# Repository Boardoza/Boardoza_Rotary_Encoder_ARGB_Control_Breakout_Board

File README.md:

# Boardoza Rotary Encoder EC1101S Breakout Board

The **Boardoza Rotary Encoder EC1101S Breakout Board** is a multifunctional input and visual feedback solution that combines a **mechanical rotary encoder with an integrated push button** and **addressable RGB LEDs (ARGB)** on a single compact PCB. This board converts rotational motion into digital signals while simultaneously enabling dynamic visual effects through programmable LEDs.

By integrating **14 cascaded ARGB LEDs** directly around the encoder, the board allows users to visually represent rotation, direction, speed, or system states. Each encoder movement can be interpreted by a microcontroller (such as Arduino, ESP32, or similar platforms) to control LED color, brightness, and animation patterns, making it ideal for interactive interfaces, control panels, and creative electronics projects.

## [Click here to purchase!](https://www.ozdisan.com/ureticiler/boardoza)

| Front Side | Back Side |
|:---:|:---:|
|  |  |

---

## Key Features

- **Rotary Encoder with Push Button:** Mechanical rotary encoder with integrated momentary push button for menu navigation and user input.
- **Integrated Addressable RGB LEDs:** Features 14 cascaded ARGB LEDs for dynamic visual feedback and animation effects.
- **Quadrature Output Signals:** Provides A and B channel outputs for accurate direction and rotation detection.
- **Visual Motion Representation:** Encoder rotation can be visually expressed through programmable LED color, pattern, and brightness changes.
- **Wide Logic Compatibility:** Fully compatible with both 3.3 V and 5 V microcontroller systems.
- **Expandable LED Chain:** ARGB data and clock input/output pins allow cascading with additional LED boards.
- **20 Pulses per Revolution:** Provides 20 pulses per 360° rotation (per phase) for precise rotational detection.

---

## Technical Specifications  

**Model:** Rotary Encoder EC1101S  
**Manufacturer:** Boardoza  
**Encoder Type:** Mechanical rotary encoder with push button  
**LED Type:** Addressable RGB (ARGB)  
**Number of LEDs:** 14  
**LED Interface:** Serial Data (DIN/DOUT), Clock (CIN/COUT)  
**Signal Outputs:** Encoder A, Encoder B, Push Button (SW)  
**Input Voltage:** 3.3 V / 5 V  
**Logic Level:** 3.3 V / 5 V compatible  
**Operating Temperature:** -40 °C to +85 °C  
**Board Dimensions:** 40 mm × 40 mm  

---

## Board Pinout

### **( J1 ) Main Connector**

| Pin Number | Pin Name | Description |
|:---:|:---:|---|
| 1 | VCC (3V3–5V) | Power supply input |
| 2 | SW | Encoder push button output (Active Low) |
| 3 | DOUT | ARGB serial data output |
| 4 | COUT | ARGB clock output |
| 5 | CIN | ARGB clock input |
| 6 | DIN | ARGB serial data input |
| 7 | Terminal_B | Encoder B channel output |
| 8 | Terminal_A | Encoder A channel output |
| 9 | GND | Ground |

---

## Board Dimensions

---

## Step Files

[Boardoza ROTARY ENCODER.step](./assets/B-ROTARY%20ENCODER_EC1101S%20Step.step)

---

## Datasheet

- [PLCC IC + RGB LEDs Datasheet.pdf](./assets/PLCC%20IC+RGB%20LEDs%20Datasheet.pdf)  
- [ROTARY ENCODER EC1101S Breakout Datasheet.pdf](./assets/B-ROTARY%20ENCODER_EC1101S%20Datasheet.pdf)

---

## Version History

- **V1.0.0** – Initial Release

---

## Support

- For questions or technical support, please contact **support@boardoza.com**

---

## **License**

This repository contains both hardware and software components:

### **Hardware Design**

[![CC BY-SA 4.0][cc-by-sa-shield]][cc-by-sa]

All hardware design files are licensed under [Creative Commons Attribution-ShareAlike 4.0 International License][cc-by-sa].

[cc-by-sa]: http://creativecommons.org/licenses/by-sa/4.0/
[cc-by-sa-shield]: https://img.shields.io/badge/License-CC%20BY--SA%204.0-lightgrey.svg

### **Software/Firmware**

[![BSD-3-Clause][bsd-shield]][bsd]

All software and firmware are licensed under [BSD 3-Clause License][bsd].

[bsd]: https://opensource.org/licenses/BSD-3-Clause
[bsd-shield]: https://img.shields.io/badge/License-BSD%203--Clause-blue.svg

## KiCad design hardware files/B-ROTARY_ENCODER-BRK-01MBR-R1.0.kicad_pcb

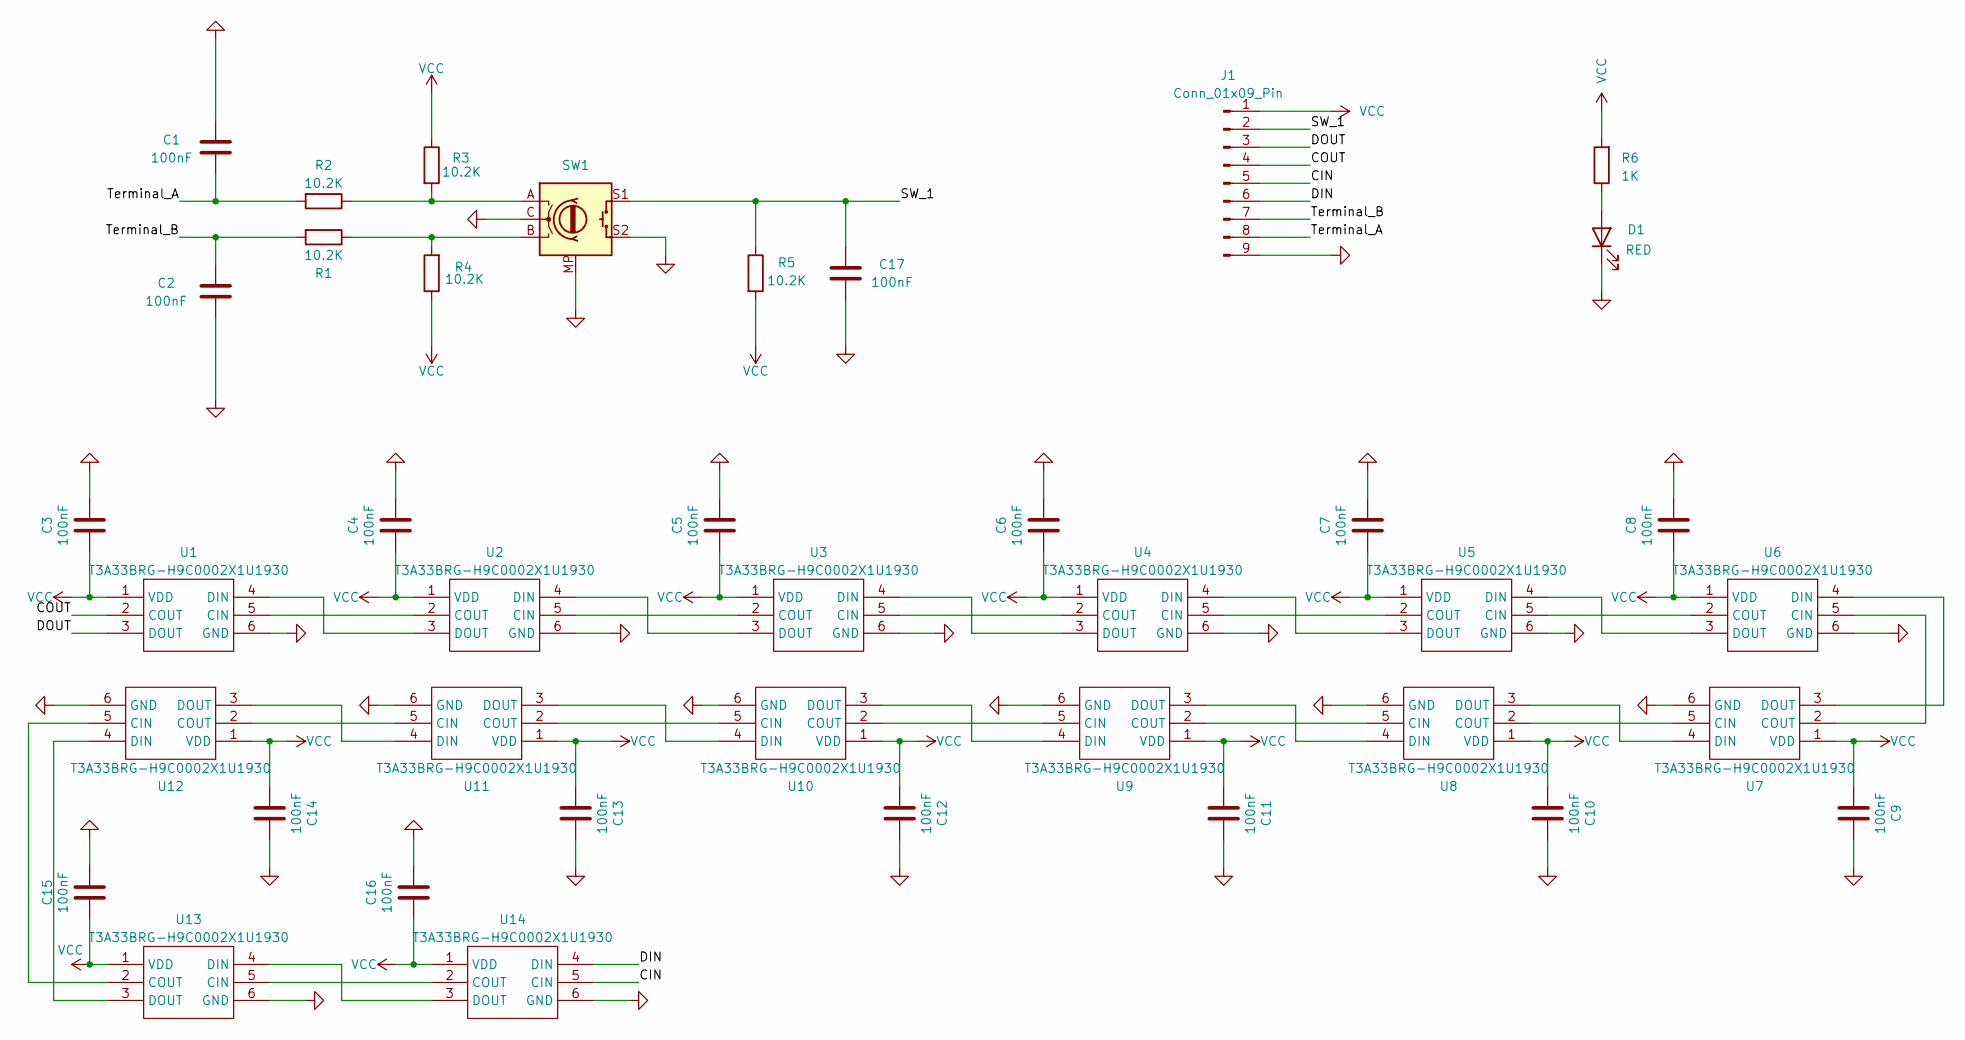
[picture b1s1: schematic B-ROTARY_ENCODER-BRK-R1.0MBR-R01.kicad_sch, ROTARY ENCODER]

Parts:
C1, C2, C3, C4, C5, C6, C7, C8, C9, C10, C11, C12, C13, C14, C15, C16, C17: 100nF; C_0603_1608Metric_Pad1.08x0.95mm_HandSolder; MPN CL10B104KB8NNNC
D1: RED; LED_0603_1608Metric; MPN LTST-C190KRKT
J1: Conn_01x09_Pin; PinHeader_1x09_P2.54mm_Vertical; MPN DS1021-1X9SF11-B
R1, R2, R3, R4, R5: 10.2K; R_0603_1608Metric; MPN 0603SAF1022T5E
R6: 1K; R_0603_1608Metric; MPN RC0603JR-071KL
SW1: RotaryEncoder_Switch_MP; L-KLS4-EC1123S-E-5A-F20; MPN L-KLS4-EC1123S-E-5A-F20
U1, U2, U3, U4, U5, U6, U7, U8, U9, U10, U11, U12, U13, U14: T3A33BRG-H9C0002X1U1930; ARGB_T3A33BRG-H9C0002X1U1930; MPN T3A33BRG-H9C0002X1U1930

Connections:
/CIN: J1.5, U14.5 (CIN)
/COUT: J1.4, U1.2 (COUT)
/DIN: J1.6, U14.4 (DIN)
/DOUT: J1.3, U1.3 (DOUT)
/SW_1: C17.2, J1.2, R5.1, SW1.S1
/Terminal_A: C1.1, J1.8, R2.2
/Terminal_B: C2.2, J1.7, R1.2
GND: C1.2, C2.1, C3.2, C4.2, C5.2, C6.2, C7.2, C8.2, C9.2, C10.2, C11.2, C12.2, C13.2, C14.2, C15.2, C16.2, C17.1, D1.1 (K), J1.9, SW1.C, SW1.MP, SW1.S2, U1.6 (GND), U2.6 (GND), U3.6 (GND), U4.6 (GND), U5.6 (GND), U6.6 (GND), U7.6 (GND), U8.6 (GND), U9.6 (GND), U10.6 (GND), U11.6 (GND), U12.6 (GND), U13.6 (GND), U14.6 (GND)
unnamed: D1.2 (A), R6.1
unnamed: R1.1, R4.2, SW1.B
unnamed: R2.1, R3.2, SW1.A
unnamed: U1.5 (CIN), U2.2 (COUT)
unnamed: U1.4 (DIN), U2.3 (DOUT)
unnamed: U2.5 (CIN), U3.2 (COUT)
unnamed: U2.4 (DIN), U3.3 (DOUT)
unnamed: U3.5 (CIN), U4.2 (COUT)
unnamed: U3.4 (DIN), U4.3 (DOUT)
unnamed: U4.5 (CIN), U5.2 (COUT)
unnamed: U4.4 (DIN), U5.3 (DOUT)
unnamed: U5.5 (CIN), U6.2 (COUT)
unnamed: U5.4 (DIN), U6.3 (DOUT)
unnamed: U6.5 (CIN), U7.2 (COUT)
unnamed: U6.4 (DIN), U7.3 (DOUT)
unnamed: U7.5 (CIN), U8.2 (COUT)
unnamed: U7.4 (DIN), U8.3 (DOUT)
unnamed: U8.5 (CIN), U9.2 (COUT)
unnamed: U8.4 (DIN), U9.3 (DOUT)
unnamed: U10.5 (CIN), U11.2 (COUT)
unnamed: U9.5 (CIN), U10.2 (COUT)
unnamed: U10.4 (DIN), U11.3 (DOUT)
unnamed: U9.4 (DIN), U10.3 (DOUT)
unnamed: U11.5 (CIN), U12.2 (COUT)
unnamed: U11.4 (DIN), U12.3 (DOUT)
unnamed: U12.5 (CIN), U13.2 (COUT)
unnamed: U12.4 (DIN), U13.3 (DOUT)
unnamed: U13.5 (CIN), U14.2 (COUT)
unnamed: U13.4 (DIN), U14.3 (DOUT)
VCC: C3.1, C4.1, C5.1, C6.1, C7.1, C8.1, C9.1, C10.1, C11.1, C12.1, C13.1, C14.1, C15.1, C16.1, J1.1, R3.1, R4.1, R5.2, R6.2, U1.1 (VDD), U2.1 (VDD), U3.1 (VDD), U4.1 (VDD), U5.1 (VDD), U6.1 (VDD), U7.1 (VDD), U8.1 (VDD), U9.1 (VDD), U10.1 (VDD), U11.1 (VDD), U12.1 (VDD), U13.1 (VDD), U14.1 (VDD)

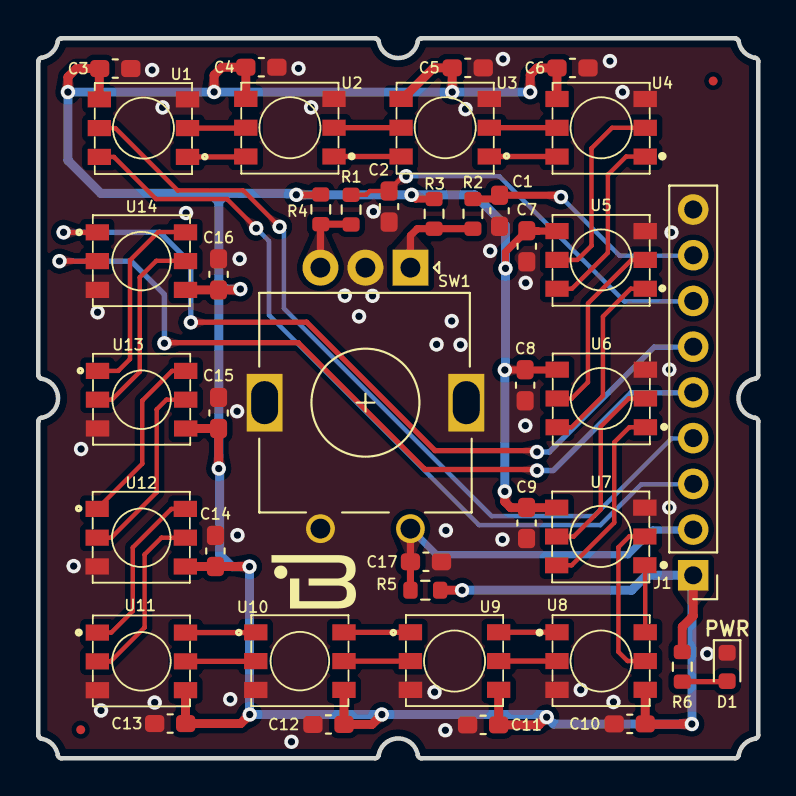
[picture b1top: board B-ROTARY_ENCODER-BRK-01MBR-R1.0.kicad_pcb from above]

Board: 2 copper layers, 40.0 x 40.0 mm, 40 parts (0 on the bottom side), 38 nets.

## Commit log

2026-04-28 Refactor comments for EC1101S.cpp
    Updated comments in EC1101S.cpp for clarity and consistency.
